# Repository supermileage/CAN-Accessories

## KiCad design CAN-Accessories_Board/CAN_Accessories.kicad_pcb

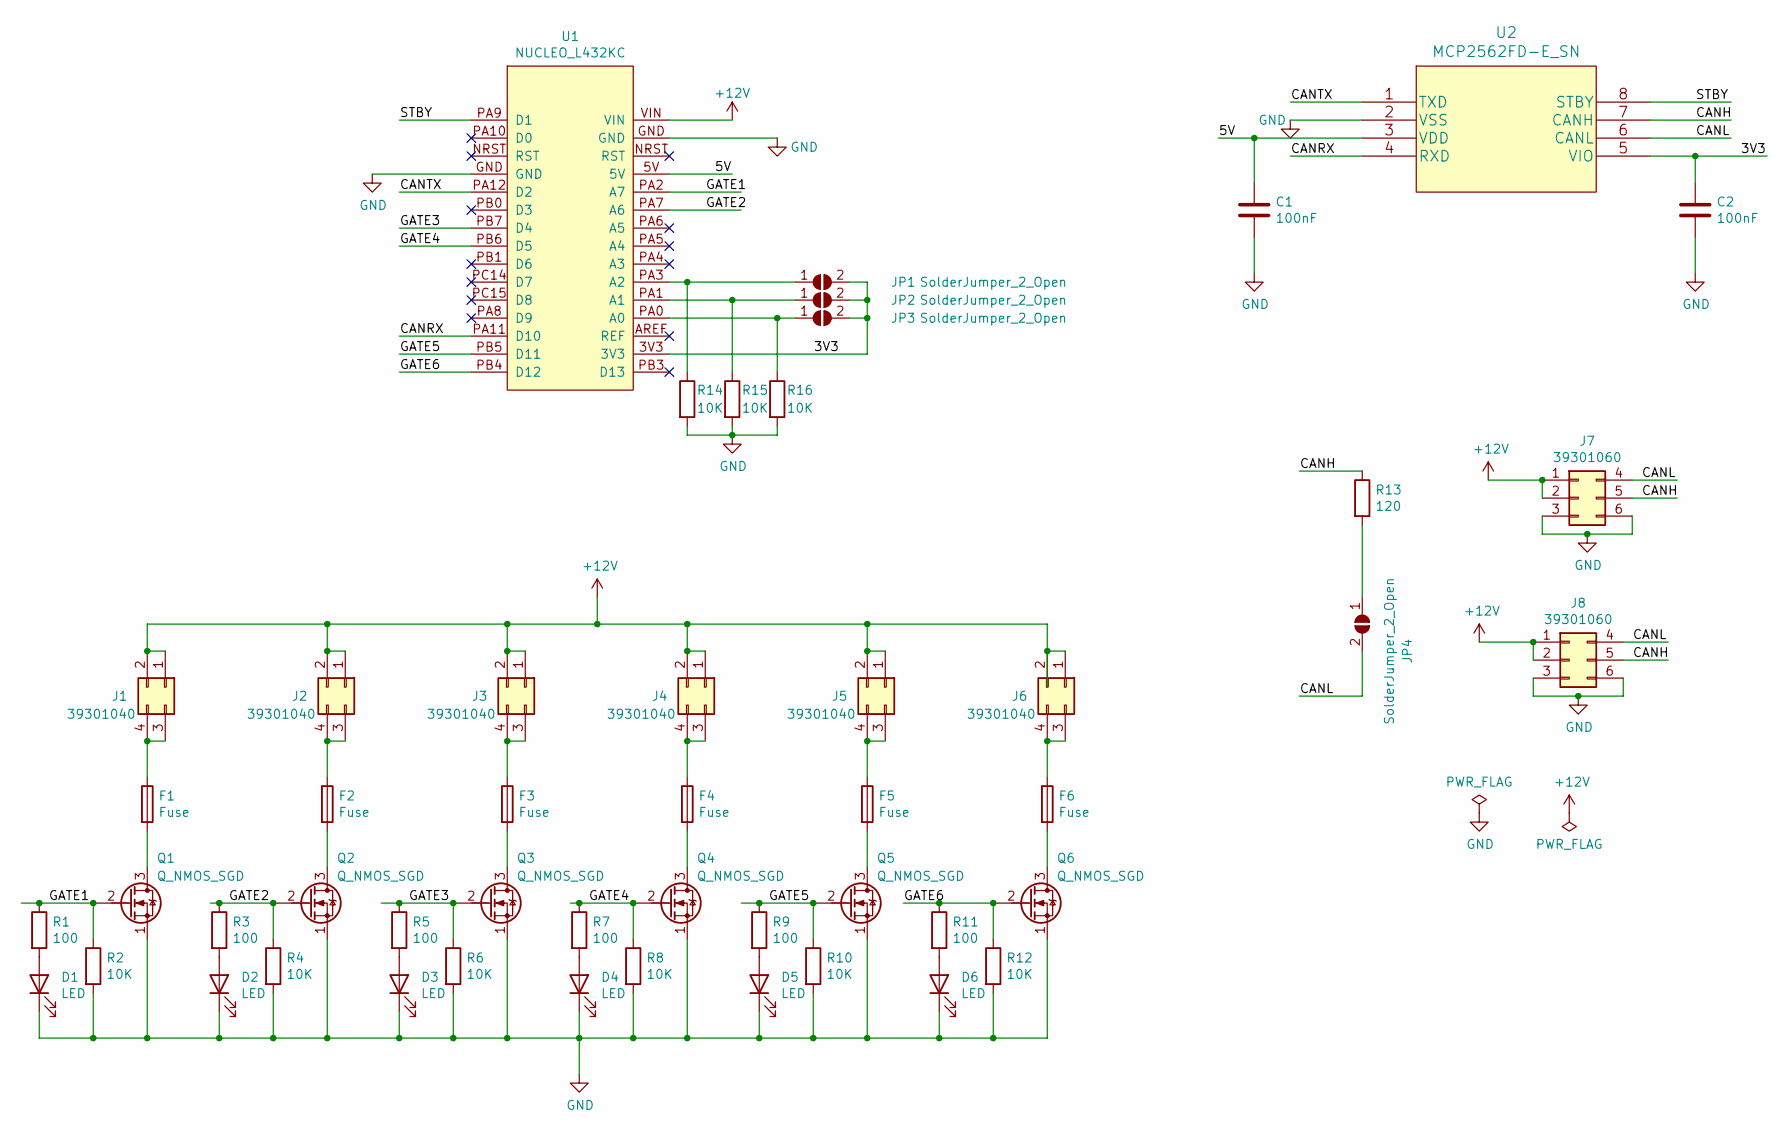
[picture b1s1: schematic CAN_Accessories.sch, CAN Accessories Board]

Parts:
C1, C2: 100nF; C_0805_2012Metric
D1, D2, D3, D4, D5, D6: LED; LED_0805_2012Metric
F1, F2, F3, F4, F5, F6: Fuse; 3586KTR
J1, J2, J3, J4, J5, J6: 39301040; Molex_Mini-Fit_Jr_5569-04A2_2x02_P4.20mm_Horizontal
J7, J8: 39301060; Molex_Mini-Fit_Jr_5569-06A2_2x03_P4.20mm_Horizontal
JP1, JP2, JP3, JP4: SolderJumper_2_Open; SolderJumper-2_P1.3mm_Open_Pad1.0x1.5mm
Q1, Q2, Q3, Q4, Q5, Q6: Q_NMOS_SGD; SOIC-8-1EP_3.9x4.9mm_P1.27mm_EP2.29x3mm
R1, R3, R5, R7, R9, R11: 100; R_0805_2012Metric
R2, R4, R6, R8, R10, R12, R14, R15, R16: 10K; R_0805_2012Metric
R13: 120; R_0805_2012Metric
U1: NUCLEO_L432KC; MODULE_NUCLEO-L432KC
U2: MCP2562FD-E_SN

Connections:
+12V: J1.1, J1.2, J2.1, J2.2, J3.1, J3.2, J4.1, J4.2, J5.1, J5.2, J6.1, J6.2, J7.1, J7.2, J8.1, J8.2, U1.VIN
/3V3: C2.1, JP1.2 (B), JP2.2 (B), JP3.2 (B), U1.3V3, U2.5 (VIO)
/5V: C1.1, U1.5V, U2.3 (VDD)
/CANH: J7.5, J8.5, R13.1, U2.7 (CANH)
/CANL: J7.4, J8.4, JP4.2 (B), U2.6 (CANL)
/CANRX: U1.PA11 (D10), U2.4 (RXD)
/CANTX: U1.PA12 (D2), U2.1 (TXD)
/GATE1: Q1.2 (G), R1.1, R2.1, U1.PA2 (A7)
/GATE2: Q2.2 (G), R3.1, R4.1, U1.PA7 (A6)
/GATE3: Q3.2 (G), R5.1, R6.1, U1.PB7 (D4)
/GATE4: Q4.2 (G), R7.1, R8.1, U1.PB6 (D5)
/GATE5: Q5.2 (G), R9.1, R10.1, U1.PB5 (D11)
/GATE6: Q6.2 (G), R11.1, R12.1, U1.PB4 (D12)
/STBY: U1.PA9 (D1), U2.8 (STBY)
GND: C1.2, C2.2, D1.1 (K), D2.1 (K), D3.1 (K), D4.1 (K), D5.1 (K), D6.1 (K), J7.3, J7.6, J8.3, J8.6, Q1.1 (S), Q2.1 (S), Q3.1 (S), Q4.1 (S), Q5.1 (S), Q6.1 (S), R2.2, R4.2, R6.2, R8.2, R10.2, R12.2, R14.2, R15.2, R16.2, U1.GND, U2.2 (VSS)
unnamed: D1.2 (A), R1.2
unnamed: D2.2 (A), R3.2
unnamed: D3.2 (A), R5.2
unnamed: D4.2 (A), R7.2
unnamed: D5.2 (A), R9.2
unnamed: D6.2 (A), R11.2
unnamed: F1.1, J1.3, J1.4
unnamed: F1.2, Q1.3 (D)
unnamed: F2.1, J2.3, J2.4
unnamed: F2.2, Q2.3 (D)
unnamed: F3.1, J3.3, J3.4
unnamed: F3.2, Q3.3 (D)
unnamed: F4.1, J4.3, J4.4
unnamed: F4.2, Q4.3 (D)
unnamed: F5.1, J5.3, J5.4
unnamed: F5.2, Q5.3 (D)
unnamed: F6.1, J6.3, J6.4
unnamed: F6.2, Q6.3 (D)
unnamed: JP1.1 (A), R14.1, U1.PA3 (A2)
unnamed: JP2.1 (A), R15.1, U1.PA1 (A1)
unnamed: JP3.1 (A), R16.1, U1.PA0 (A0)
unnamed: JP4.1 (A), R13.2

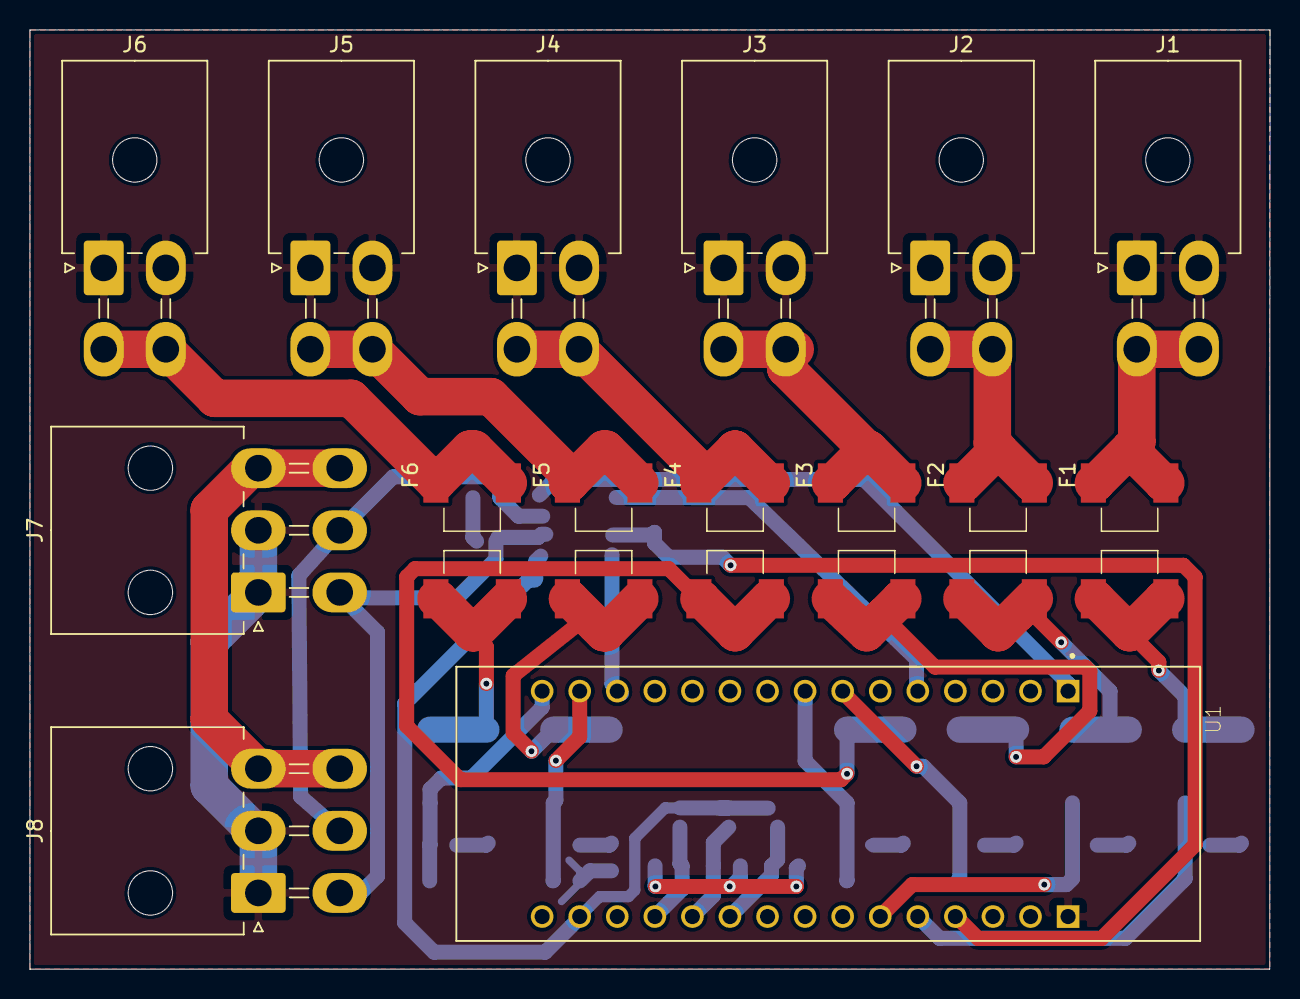
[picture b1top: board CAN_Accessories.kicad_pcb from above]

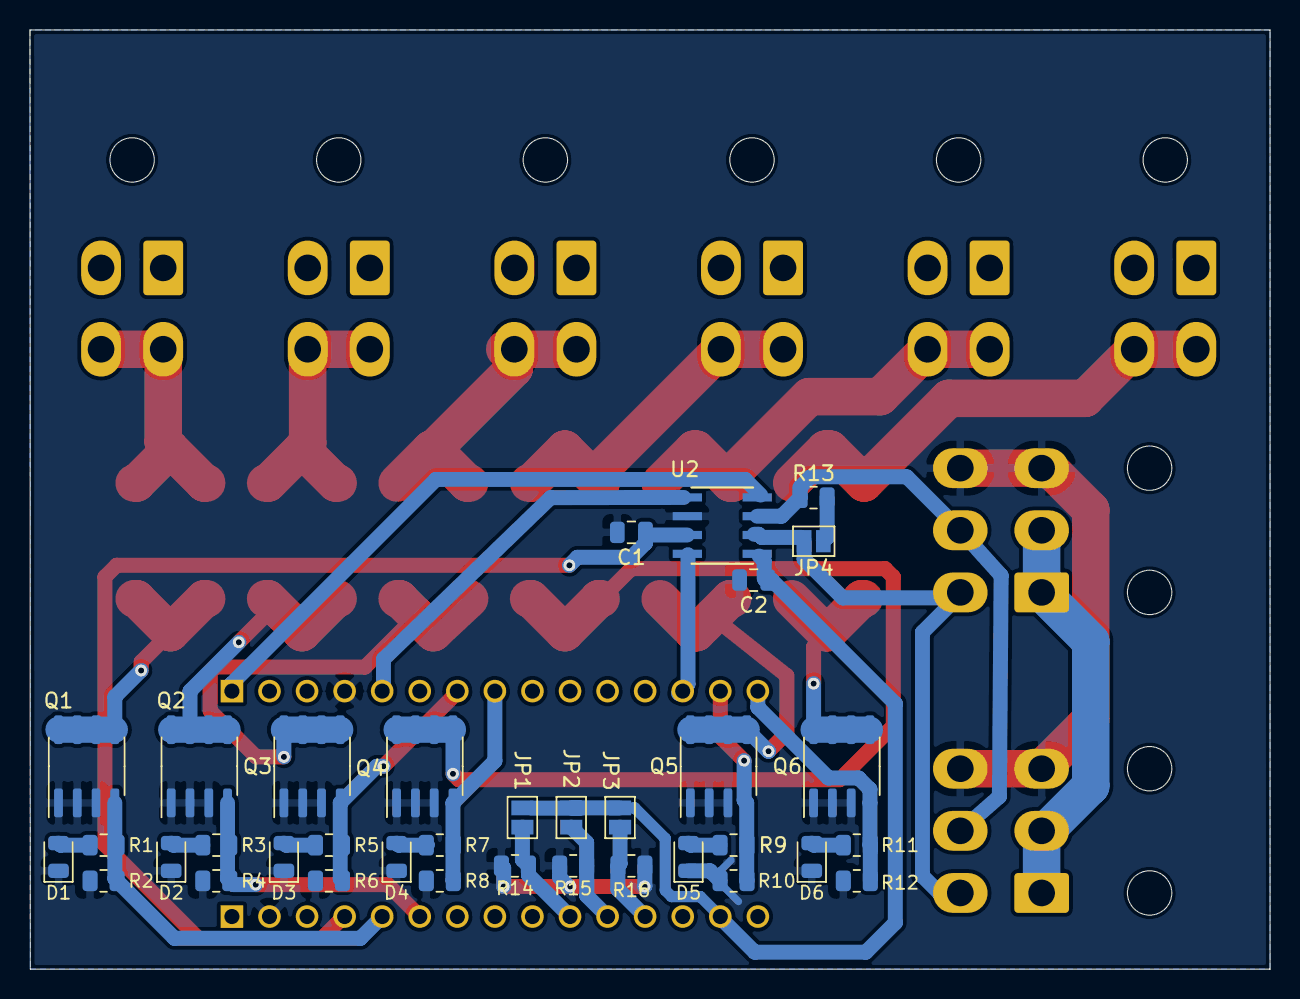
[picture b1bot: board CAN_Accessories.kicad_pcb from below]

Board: 2 copper layers, 83.8 x 63.5 mm, 50 parts (35 on the bottom side), 37 nets.

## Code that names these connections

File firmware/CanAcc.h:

#ifndef CANACC_H
#define CANACC_H

#include "mbed.h"

// Gate connections
#define GATE1       PA_2      // Disables USB Serial
#define GATE2       PA_7
#define GATE3       PB_7
#define GATE4       PB_6
#define GATE5       PB_5
#define GATE6       PB_4

#define ACCESSORIES_CAN_ID 0x60

#define STATUS_PERIOD 1.0     // time in seconds between sending status updates

namespace CanAcc
{
    struct AccInfo{
        int id;
        int board;
        char name[32];
        bool initial_state;
        bool blinks;
        unsigned int gate;
    };

    // TODO: convert these into the macros
    /* 
     * {id, boards, name, blinks, gates}
     * id: Included in CAN message to identify accessory
     * boards: one-hot encoded value to determine which boards house the
     *         accessory
     * name: name of the accessory - used for serial output
     * blinks: whether the accesory blinks.
     * gates - index of gate in gates[] which accessory is attached to
     */
    constexpr AccInfo acc_info_list[] = {
        // {id, boards, name, blinks, gates}
        {0, 0b11, "Headlights / Running lights", 0, false, 1},
        {1, 0b10, "Brakelights", 0, false, 2},
        {2, 0b01, "Horn", 0, false, 3},
        {4, 0b11, "Right Indicators", 1, true, 4},
        {5, 0b11, "Left Indicators", 1, true, 5},
        {6, 0b01, "Wipers", 0, false, 2}
    };

    constexpr PinName gates[] = {
        PA_2,
        PA_7,
        PB_7,
        PB_6,
        PB_5,
        PB_4
    };
}

// CAN connections
#define CAN_RX      PA_11
#define CAN_TX      PA_12
#define CAN_STBY    PA_9

// Board Select Solder Bridge Connections
#define BOARD_SEL_0 PA_0
#define BOARD_SEL_1 PA_1
#define BOARD_SEL_2 PA_3        // Disables USB Serial

// Blinkrate for blinking accessories:
#define BLINK_RATE  0.5

// Misc
#define LED         LED3

#endif

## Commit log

2020-11-26 test
2021-01-22 schematics and pcb
2021-01-22 Sample code implementing Ticker
2021-01-23 Adding CAN Handler files
2021-01-28 removed files
2021-01-28 Restructered Code
2021-01-28 removed test files
2021-01-29 Fixed error on line 40
2021-01-30 Changed Wipers to non-blinking
2021-01-30 Files and removed compiler from source folder
2021-02-13 Added blink attribute to Accessory, and merged can hander for loops
2021-02-13 moved ticker functionality to Accessories object
2021-02-13 made accessory ids separate from array index
2021-02-13 Bug Squashing WOW I'm terrible at c++
2021-03-06 Bugs exterminated, and misc tools created CAN MESSAGE HANDLER is in fully functional state. Debug tools created: - SerialRec - Receives 8 bit CAN messages and sends over Serial. - SerialSend - Takes 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
2021-03-13 Added KiCAD files for CAN Accessories
2021-03-13 Changed layout
2021-03-13 Changed PCB Layout
2021-03-21 Fixed file name
2021-03-23 Changed footprints from 0603 to 0805
2021-04-03 implements operation switch in CanHandler
    implements CAN filter
    implements operation 1 - toggle
    changes SerialRev and SerialSend to work with multi-byte messages
2021-04-08 Implemented Board Identification
2022-02-15 firmware working! (for simple on/off)
2022-03-17 party operation mode
2022-03-17 QOL changes, more macro usage

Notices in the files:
parts and their libraries:
Copyright 2016 Accelerated Designs. All rights reserved.
